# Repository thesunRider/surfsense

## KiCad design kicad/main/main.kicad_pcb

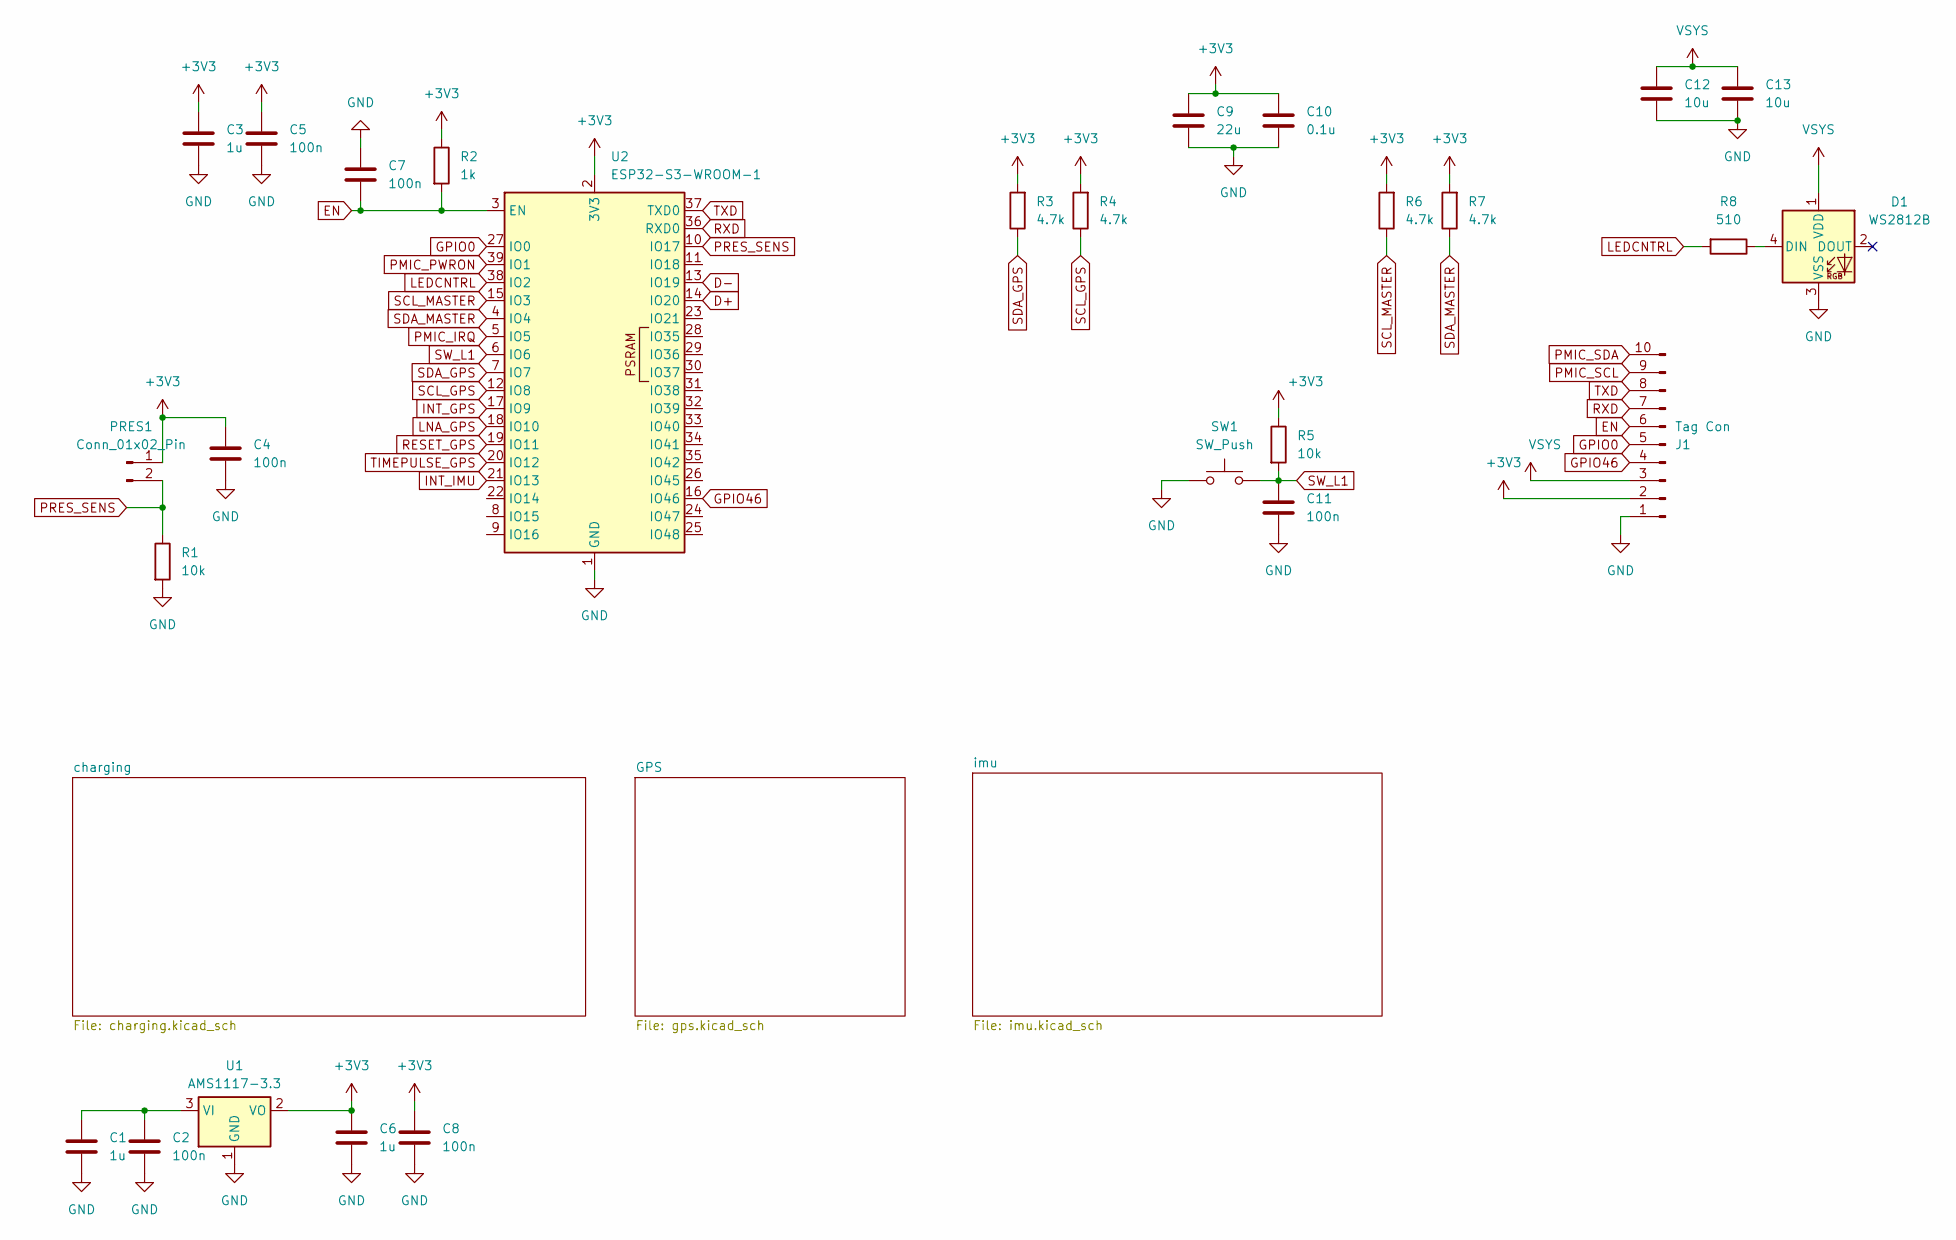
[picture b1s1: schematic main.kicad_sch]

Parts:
C1, C3, C6: 1u; C_0805_2012Metric
C2, C4, C5, C7, C8: 100n; C_0805_2012Metric
C9: 22u; C_0603_1608Metric_Pad1.08x0.95mm_HandSolder
C10: 0.1u; C_0603_1608Metric_Pad1.08x0.95mm_HandSolder
C11: 100n; C_0402_1005Metric; Mfr. # CL05B104KO5NNNC; LCSC Part # C1525
C12, C13: 10u; C_0603_1608Metric_Pad1.08x0.95mm_HandSolder
D1: WS2812B; LED_WS2812B_PLCC4_5.0x5.0mm_P3.2mm; Mfr Part XL-5050RGBC-WS2812B-S; LCSC Part C22461793
J1: Tag Con; TAG-CONNECT_TC2050-IDC
PRES1: Conn_01x02_Pin; SMD_CONNECTOR_PAD
R1, R5: 10k; R_0603_1608Metric_Pad0.98x0.95mm_HandSolder
R2: 1k
R3, R4, R6, R7: 4.7k; R_0603_1608Metric_Pad0.98x0.95mm_HandSolder
R8: 510; R_0603_1608Metric_Pad0.98x0.95mm_HandSolder
SW1: SW_Push; SW_SPST_B3S-1000; Mfr Part B3S-1000; LCSC Part C2733655
U1: AMS1117-3.3; SOT-223-3_TabPin2
U2: ESP32-S3-WROOM-1

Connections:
+3V3: C3.1, C4.1, C5.1, C6.1, C8.1, C9.1, C10.1, J1.2, PRES1.1, R2.1, R3.2, R4.2, R5.1, R6.2, R7.2, U1.2 (VO), U2.2 (3V3); also elsewhere on the board
D+: U2.14 (IO20); also elsewhere on the board
D-: U2.13 (IO19); also elsewhere on the board
EN: C7.2, J1.6, R2.2, U2.3 (EN)
GND: C1.2, C2.2, C3.2, C4.2, C5.2, C6.2, C7.1, C8.2, C9.2, C10.2, C11.2, C12.1, C13.1, D1.3 (VSS), J1.1, R1.2, SW1.1, U1.1 (GND), U2.1 (GND), U2.40 (GND), U2.41 (GND); also elsewhere on the board
GPIO0: J1.5, U2.27 (IO0)
GPIO46: J1.4, U2.16 (IO46)
INT_GPS: U2.17 (IO9); also elsewhere on the board
INT_IMU: U2.21 (IO13); also elsewhere on the board
LEDCNTRL: R8.2, U2.38 (IO2)
LNA_GPS: U2.18 (IO10); also elsewhere on the board
unnamed: D1.4 (DIN), R8.1
unnamed: C1.1, C2.1, U1.3 (VI)
PMIC_IRQ: U2.5 (IO5); also elsewhere on the board
PMIC_PWRON: U2.39 (IO1); also elsewhere on the board
PRES_SENS: PRES1.2, R1.1, U2.10 (IO17)
RESET_GPS: U2.19 (IO11); also elsewhere on the board
RXD: J1.7, U2.36 (RXD0)
SCL_GPS: R4.1, U2.12 (IO8); also elsewhere on the board
SCL_MASTER: R6.1, U2.15 (IO3); also elsewhere on the board
SDA_GPS: R3.1, U2.7 (IO7); also elsewhere on the board
SDA_MASTER: R7.1, U2.4 (IO4); also elsewhere on the board
SW_L1: C11.1, R5.2, SW1.2, U2.6 (IO6)
TIMEPULSE_GPS: U2.20 (IO12); also elsewhere on the board
TXD: J1.8, U2.37 (TXD0)
VSYS: C12.2, C13.2, D1.1 (VDD), J1.3; also elsewhere on the board

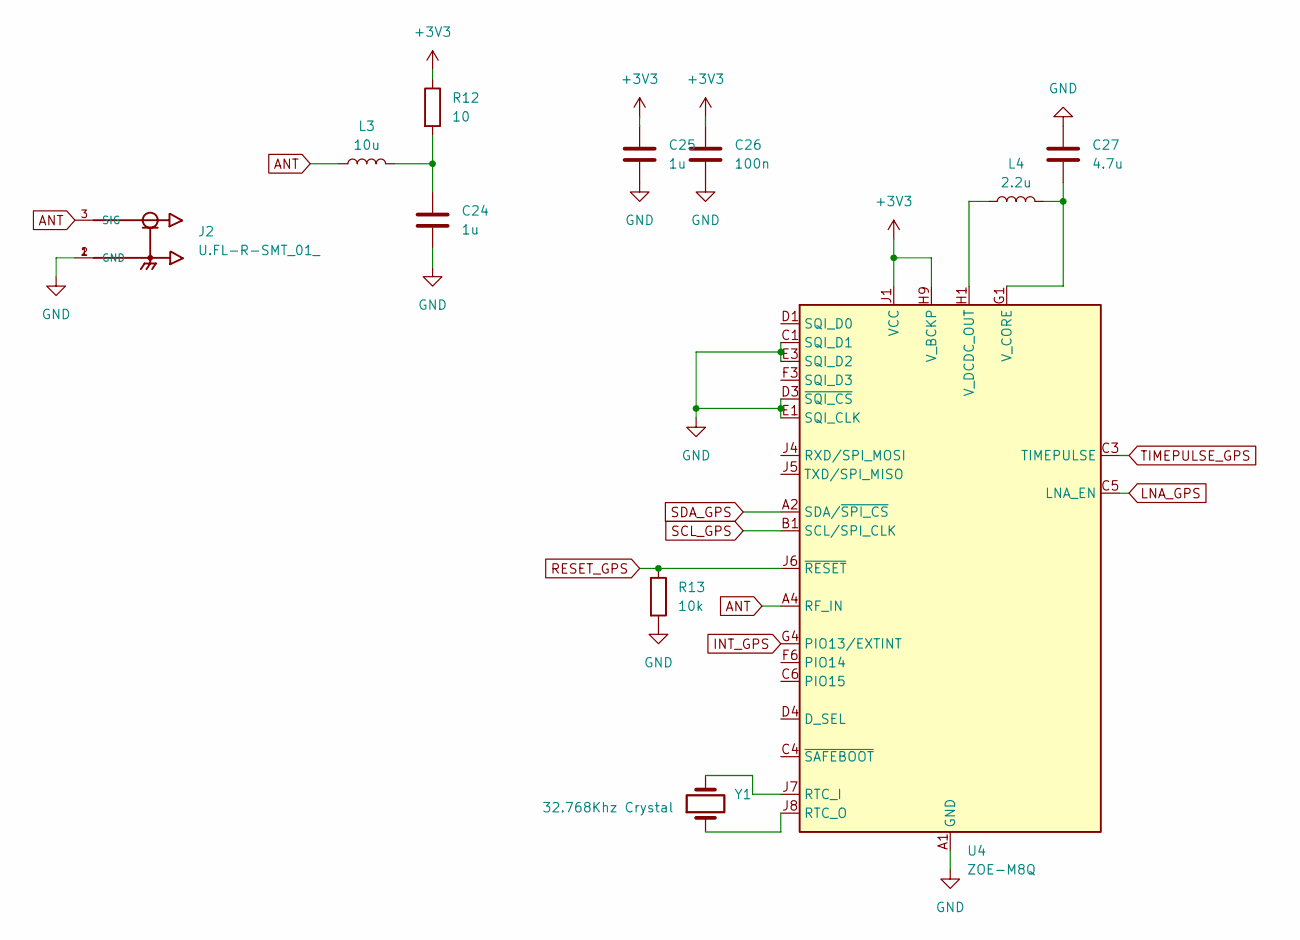
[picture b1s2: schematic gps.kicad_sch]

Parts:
C24, C25: 1u; C_0805_2012Metric
C26: 100n; C_0805_2012Metric
C27: 4.7u; C_0805_2012Metric
J2: U.FL-R-SMT_01_; HRS_U.FL-R-SMT_01_
L3: 10u; L_0805_2012Metric_Pad1.05x1.20mm_HandSolder; Mfr Part AHW2012F-1R0KTF; LCSC Part C6364721
L4: 2.2u; L_0805_2012Metric_Pad1.05x1.20mm_HandSolder; Mfr Part AHW2012F-1R0KTF; LCSC Part C6364721
R12: 10
R13: 10k
U4: ZOE-M8Q; ublox_ZOE_M8
Y1: 32.768Khz Crystal; Crystal_SMD_Abracon_ABM3-2Pin_5.0x3.2mm

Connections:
+3V3: C25.1, C26.1, R12.1, U4.H9 (V_BCKP), U4.J1 (VCC), U4.J2 (VCC); also elsewhere on the board
ANT: J2.3 (SIG), L3.1, U4.A4 (RF_IN)
GND: C24.2, C25.2, C26.2, C27.1, J2.1 (GND), J2.2 (GND), R13.2, U4.A1 (GND), U4.A3 (GND), U4.A5 (GND), U4.A7 (GND), U4.A8 (GND), U4.A9 (GND), U4.B9 (GND), U4.C1 (SQI_D1), U4.C7 (GND), U4.C9 (GND), U4.D3 (~SQI_CS), U4.D6 (GND), U4.D9 (GND), U4.E1 (SQI_CLK), U4.E3 (SQI_D2), U4.E7 (GND), U4.F7 (GND), U4.G3 (GND), U4.G6 (GND), U4.G7 (GND), U4.J3 (GND), U4.J9 (GND); also elsewhere on the board
INT_GPS: U4.G4 (PIO13/EXTINT); also elsewhere on the board
LNA_GPS: U4.C5 (LNA_EN); also elsewhere on the board
unnamed: C24.1, L3.2, R12.2
unnamed: U4.J7 (RTC_I), Y1.2
unnamed: U4.J8 (RTC_O), Y1.1
unnamed: C27.2, L4.2, U4.G1 (V_CORE)
unnamed: L4.1, U4.H1 (V_DCDC_OUT)
RESET_GPS: R13.1, U4.J6 (~RESET); also elsewhere on the board
SCL_GPS: U4.B1 (SCL/SPI_CLK); also elsewhere on the board
SDA_GPS: U4.A2 (SDA/~SPI_CS); also elsewhere on the board
TIMEPULSE_GPS: U4.C3 (TIMEPULSE); also elsewhere on the board

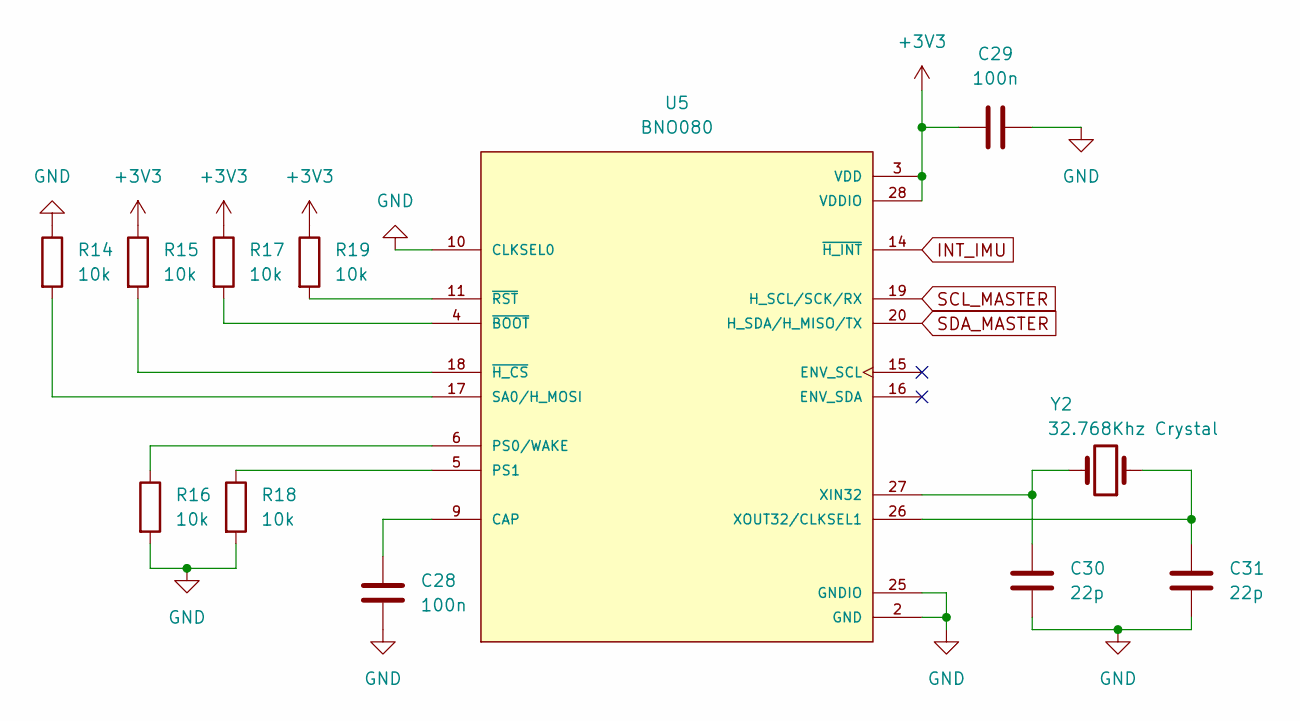
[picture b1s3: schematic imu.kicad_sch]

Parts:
C28, C29: 100n; C_0805_2012Metric
C30, C31: 22p; C_0805_2012Metric
R14, R15, R16, R17, R18, R19: 10k; R_0603_1608Metric_Pad0.98x0.95mm_HandSolder
U5: BNO080; LGA-28_5.2x3.8mm_P0.5mm; PARTREV 1.6
Y2: 32.768Khz Crystal; Crystal_SMD_Abracon_ABM3-2Pin_5.0x3.2mm

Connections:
+3V3: C29.1, R15.1, R17.1, R19.1, U5.3 (VDD), U5.28 (VDDIO); also elsewhere on the board
GND: C28.1, C29.2, C30.1, C31.1, R14.1, R16.2, R18.2, U5.2 (GND), U5.10 (CLKSEL0), U5.25 (GNDIO); also elsewhere on the board
INT_IMU: U5.14 (~H_INT); also elsewhere on the board
unnamed: C28.2, U5.9 (CAP)
unnamed: R16.1, U5.6 (PS0/WAKE)
unnamed: R18.1, U5.5 (PS1)
unnamed: R14.2, U5.17 (SA0/H_MOSI)
unnamed: C30.2, U5.27 (XIN32), Y2.2
unnamed: C31.2, U5.26 (XOUT32/CLKSEL1), Y2.1
unnamed: R17.2, U5.4 (~BOOT)
unnamed: R15.2, U5.18 (~H_CS)
unnamed: R19.2, U5.11 (~RST)
SCL_MASTER: U5.19 (H_SCL/SCK/RX); also elsewhere on the board
SDA_MASTER: U5.20 (H_SDA/H_MISO/TX); also elsewhere on the board

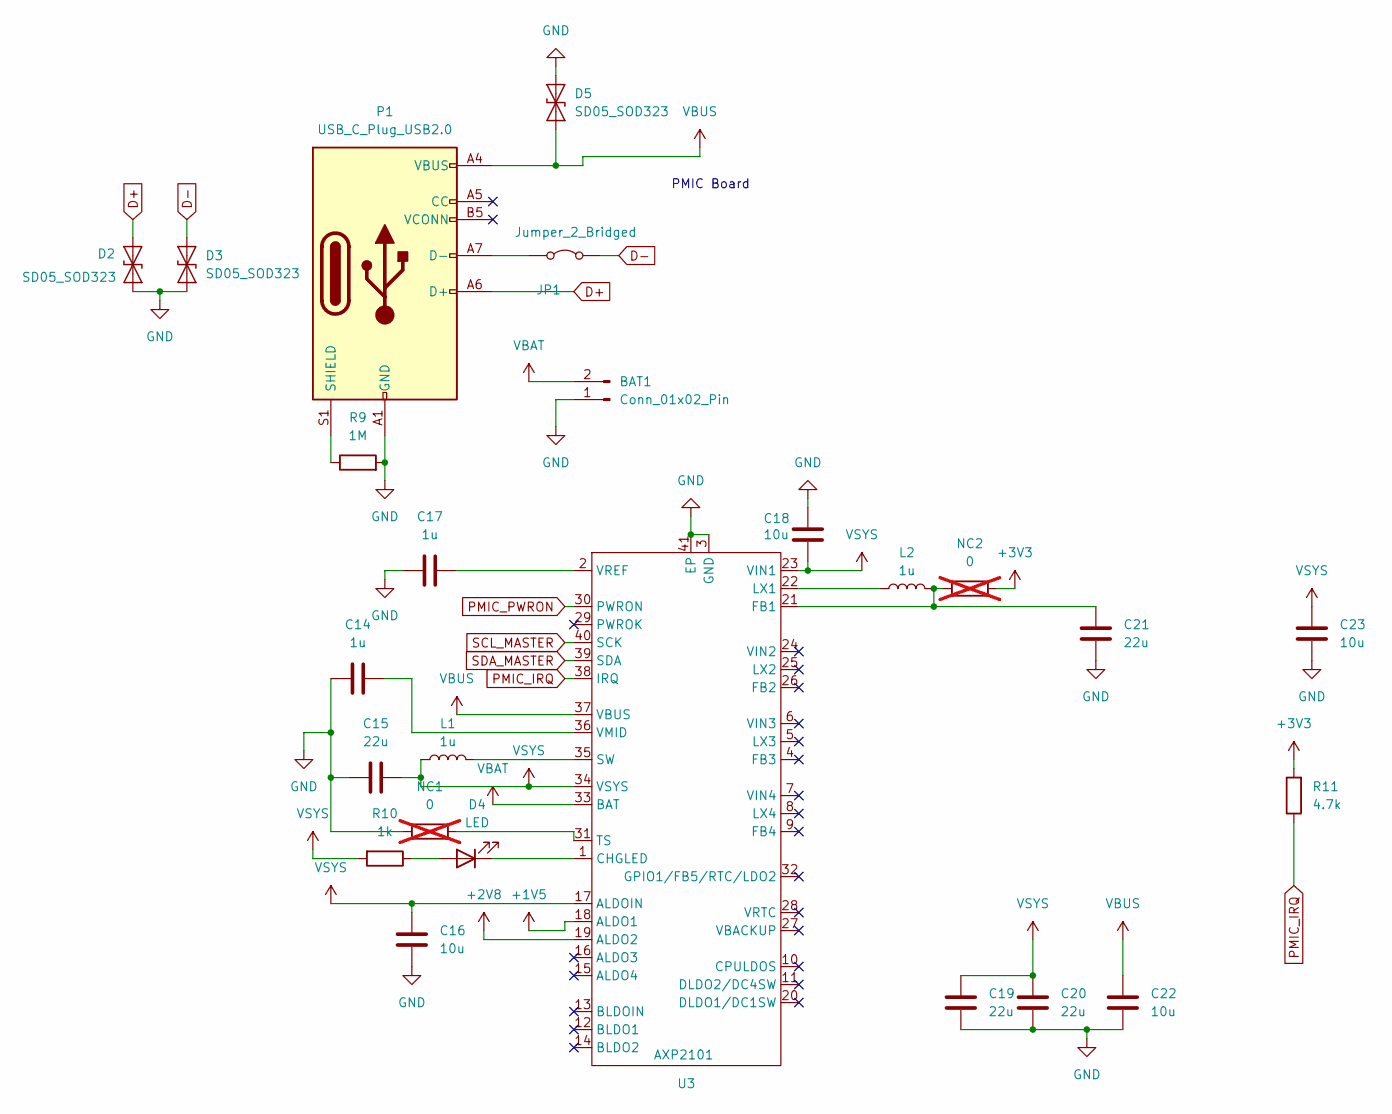
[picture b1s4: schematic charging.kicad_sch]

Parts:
BAT1: Conn_01x02_Pin; SMD_CONNECTOR_PAD
C14, C17: 1u; C_0603_1608Metric
C15, C19, C20, C21: 22u; C_0603_1608Metric_Pad1.08x0.95mm_HandSolder
C16, C18, C22, C23: 10u; C_0603_1608Metric_Pad1.08x0.95mm_HandSolder
D2, D3, D5: SD05_SOD323; D_SOD-323
D4: LED; LED_0402_1005Metric
JP1: Jumper_2_Bridged
L1, L2: 1u; L_0805_2012Metric_Pad1.05x1.20mm_HandSolder; Mfr Part AHW2012F-1R0KTF; LCSC Part C6364721
NC1, NC2: 0; R_1206_3216Metric; not fitted
P1: USB_C_Plug_USB2.0; USB_C_Receptacle_HRO_TYPE-C-31-M-12; Mfr Part TYPE-C-31-M-14; LCSC Part C223907
R9: 1M; R_0603_1608Metric_Pad0.98x0.95mm_HandSolder
R10: 1k; R_0603_1608Metric_Pad0.98x0.95mm_HandSolder
R11: 4.7k; R_0603_1608Metric_Pad0.98x0.95mm_HandSolder
U3: AXP2101; QFN-40-1EP_5x5mm_P0.4mm_EP3.6x3.6mm; Mfr Part AXP2101; LCSC Part C3036461

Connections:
+1V5: U3.18 (ALDO1)
+2V8: U3.19 (ALDO2)
+3V3: NC2.2, R11.2; also elsewhere on the board
D+: D2.2 (A2), P1.A6 (D+); also elsewhere on the board
D-: D3.2 (A2), JP1.2 (B); also elsewhere on the board
GND: BAT1.1, C14.1, C15.2, C16.1, C17.1, C18.2, C19.1, C20.1, C21.1, C22.1, C23.1, D2.1 (A1), D3.1 (A1), D5.2 (A2), NC1.1, P1.A1 (GND), P1.A12 (GND), P1.B1 (GND), P1.B12 (GND), R9.2, U3.3 (GND), U3.41 (EP); also elsewhere on the board
unnamed: D4.2 (A), R10.1
unnamed: D4.1 (K), U3.1 (CHGLED)
unnamed: JP1.1 (A), P1.A7 (D-)
unnamed: P1.S1 (SHIELD), R9.1
unnamed: C21.2, L2.2, NC2.1, U3.21 (FB1)
unnamed: L2.1, U3.22 (LX1)
unnamed: L1.2, U3.35 (SW)
unnamed: NC1.2, U3.31 (TS)
unnamed: C14.2, U3.36 (VMID)
unnamed: C17.2, U3.2 (VREF)
PMIC_IRQ: R11.1, U3.38 (IRQ); also elsewhere on the board
PMIC_PWRON: U3.30 (PWRON); also elsewhere on the board
SCL_MASTER: U3.40 (SCK); also elsewhere on the board
SDA_MASTER: U3.39 (SDA); also elsewhere on the board
VBAT: BAT1.2, U3.33 (BAT)
VBUS: C22.2, D5.1 (A1), P1.A4 (VBUS), P1.A9 (VBUS), P1.B4 (VBUS), P1.B9 (VBUS), U3.37 (VBUS)
VSYS: C15.1, C16.2, C18.1, C19.2, C20.2, C23.2, L1.1, R10.2, U3.17 (ALDOIN), U3.23 (VIN1), U3.34 (VSYS); also elsewhere on the board

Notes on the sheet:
PMIC Board

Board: 2 copper layers, 68 parts (15 on the bottom side), 47 nets, no tracks yet.

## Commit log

2025-04-02 Embedded tests
2025-04-03 Embedded main
2025-04-09 Added base
2025-04-09 Added README
2025-04-13 psuhlogs
2025-04-23 Finished and tested main
2025-04-23 Added changes
2025-04-24 Changed pin layout
2025-04-24 Added datasets and Finished prototype code
2025-04-25 Improved SD write speed by changing flush times
2025-04-25 Revised perfomance and pulling more data from GPS
2025-04-25 Updated datasets with more data
2025-04-26 added mainbase
2025-04-26 Updated proofs
2025-04-27 Added ahrs functions
2025-04-30 changed vis
2025-05-25 Added External magnetometer
2025-06-03 Added new adafruit deps
2025-06-03 Added all coms
